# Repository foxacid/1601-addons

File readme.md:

# 1601 Clone Add-Ons

This repository contains a front panel design and divider add-on (circuit design by [Matthias Herrmann aka Fonik](http://www.modular.fonik.de/)) for the [1601 clone project by Kipling](https://www.muffwiggler.com/forum/viewtopic.php?t=110640).

## One Thousand Six Hundred and One Panel 

Just like the [TTSH](http://www.thehumancomparator.net/) panel, this 1601 front panel design is inspired by the ARP 2600 'Grey Meanie' layout and colour scheme. To match the TTSH, the text is set in 9pt Helvetica (white on RAL 7016 Anthrazitgrau).

The layout fits Kiplings 1601 clone PCBS Rev 1-3. Additionally there is a provision for 6 extra jacks above the power switch to the right to accomodate the Clock Divider add-on.

## Divider PCB

The Clock Divider is based on an [original design by Matthias Herrmann](http://www.modular.fonik.de/pdf/SimpleDividerSCH.pdf) - thanks Matthias! The clock-divider folder contains the EAGLE source files and Gerbers generated with [Seeed Studio](https://www.seeedstudio.com/) design rules. A unipolar +15V power source is required.

There is a provision for normalising Gate Output 2 to the divider's clock input. There are also provisions for LED indicators and a manual Reset button. Those are not present on the front panel.

### PCB

### Bill of Materials

 - - - -
**Make sure to use 15V versions for the logic ICs**
 - - - -

Name                 |  Value       |  Package 
-----------------    | ------------ | ------------
***Capacitors***     |              |         
C1                   |  100uF       |  Radial, 2.5mm spacing
C2                   |  0.1µF       |  0805
C3                   |  0.1µF       |  0805
C5                   |  0.01µF      |  0805
***Semiconductors*** |              |         
D1-D4                |  1N4148      |  DO35 
Q1-Q7                |  BC850       |  SOT23
IC1                  |  4024D       |  SO14
IC2                  |  4069D       |  SO14
***Resistors***      |              |      
R1                   |  47K         |  0805
R2                   |  10K         |  0805
R3                   |  47K         |  0805
R4                   |  100K        |  0805
R5                   |  100K        |  0805
R6                   |  10K         |  0805
R7                   |  10K         |  0805
R8                   |  47K         |  0805
R10                  |  2K2         |  0805
R11                  |  1K          |  0805
R12                  |  2K2         |  0805
R13                  |  2K2         |  0805
R14                  |  1K          |  0805
R15                  |  2K2         |  0805
R16                  |  2K2         |  0805
R17                  |  1K          |  0805
R18                  |  2K2         |  0805
R19                  |  2K2         |  0805
R20                  |  1K          |  0805
R21                  |  2K2         |  0805
***Jacks***          |              |    
CLOCK                |  PJ301BM     |  3,5mm Mono
RESET                |  PJ301BM     |  3,5mm Mono
F/2                  |  PJ301BM     |  3,5mm Mono
F/4                  |  PJ301BM     |  3,5mm Mono
F/8                  |  PJ301BM     |  3,5mm Mono
F/16                 |  PJ301BM     |  3,5mm Mono

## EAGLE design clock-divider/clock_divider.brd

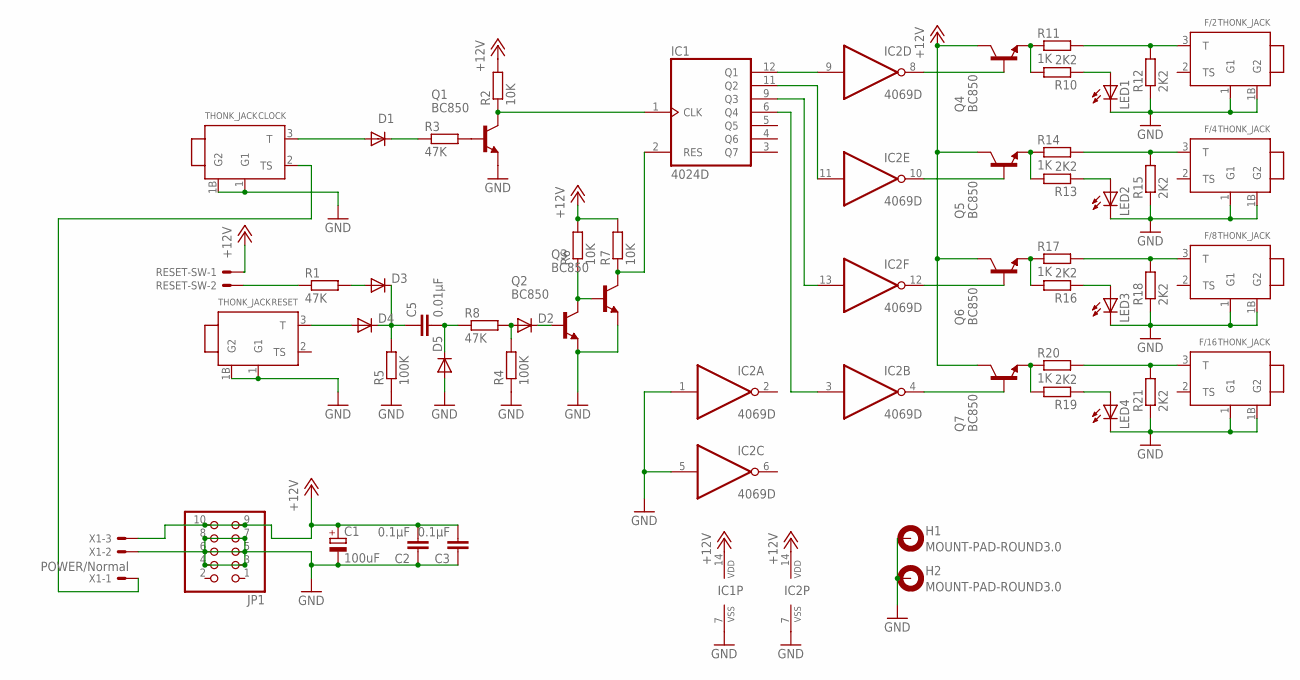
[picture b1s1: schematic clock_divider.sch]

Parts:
C1: 100uF; E2,5-6E
C2, C3: 0.1µF; C0805
C5: 0.01µF; C0805
CLOCK: THONK_JACK; THONK_JACK_P
D1, D2, D3, D4, D5: 1N4148; DO35-7
F/2, F/4, F/8, F/16: THONK_JACK; THONK_JACK_P
H1, H2: MOUNT-PAD-ROUND3.0; 3,0-PAD
IC1: 4024D; SO14
IC2: 4069D; SO14
JP1: PINHD-2X5; 2X05
LED1, LED2, LED3, LED4: LED5MM
Q1, Q2, Q3, Q4, Q5, Q6, Q7: BC850; SOT23
R1, R3, R8: 47K; M0805
R2, R6, R7: 10K; M0805
R4, R5: 100K; M0805
R10, R12, R13, R15, R16, R18, R19, R21: 2K2; M0805
R11, R14, R17, R20: 1K; M0805
RESET: THONK_JACK; THONK_JACK_P
RESET-SW: KK-156-2
X1: POWER/Normal; KK-156-3

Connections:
+12V: C1.+, C2.2, C3.2, IC1.14 (VDD), IC2.14 (VDD), JP1.9, JP1.10, Q4.3 (C), Q5.3 (C), Q6.3 (C), Q7.3 (C), R2.2, R6.2, R7.2, RESET-SW.1, X1.3
GND: C1.-, C2.1, C3.1, CLOCK.1 (G1), CLOCK.1B (G2), D5.A, F/2.1 (G1), F/2.1B (G2), F/4.1 (G1), F/4.1B (G2), F/8.1 (G1), F/8.1B (G2), F/16.1 (G1), F/16.1B (G2), H1.B3,0, H2.B3,0, IC1.7 (VSS), IC2.1 (I), IC2.5 (I), IC2.7 (VSS), JP1.3, JP1.4, JP1.5, JP1.6, JP1.7, JP1.8, LED1.K (C), LED2.K (C), LED3.K (C), LED4.K (C), Q1.2 (E), Q2.2 (E), Q3.2 (E), R4.1, R5.1, R12.1, R15.1, R18.1, R21.1, RESET.1 (G1), RESET.1B (G2), X1.2
unnamed: Q4.2 (E), R10.2, R11.1
unnamed: IC1.12 (Q1), IC2.9 (I)
unnamed: IC1.11 (Q2), IC2.11 (I)
unnamed: Q1.1 (B), R3.2
unnamed: IC1.1 (CLK), Q1.3 (C), R2.1
unnamed: D1.C, R3.1
unnamed: CLOCK.3 (T), D1.A
unnamed: D4.A, RESET.3 (T)
unnamed: C5.1, D3.C, D4.C, R5.2
unnamed: C5.2, D5.C, R8.1
unnamed: D2.A, R4.2, R8.2
unnamed: D2.C, Q2.1 (B)
unnamed: Q2.3 (C), Q3.1 (B), R6.1
unnamed: IC1.2 (RES), Q3.3 (C), R7.1
unnamed: IC1.9 (Q3), IC2.13 (I)
unnamed: IC1.6 (Q4), IC2.3 (I)
unnamed: LED2.A, R13.1
unnamed: IC2.8 (O), Q4.1 (B)
unnamed: LED4.A, R19.1
unnamed: F/4.3 (T), R14.2, R15.2
unnamed: Q5.2 (E), R13.2, R14.1
unnamed: IC2.10 (O), Q5.1 (B)
unnamed: F/8.3 (T), R17.2, R18.2
unnamed: Q6.2 (E), R16.2, R17.1
unnamed: IC2.12 (O), Q6.1 (B)
unnamed: F/16.3 (T), R20.2, R21.2
unnamed: Q7.2 (E), R19.2, R20.1
unnamed: IC2.4 (O), Q7.1 (B)
unnamed: LED3.A, R16.1
unnamed: LED1.A, R10.1
unnamed: D3.A, R1.2
unnamed: R1.1, RESET-SW.2
unnamed: CLOCK.2 (TS), X1.1
unnamed: F/2.3 (T), R11.2, R12.2

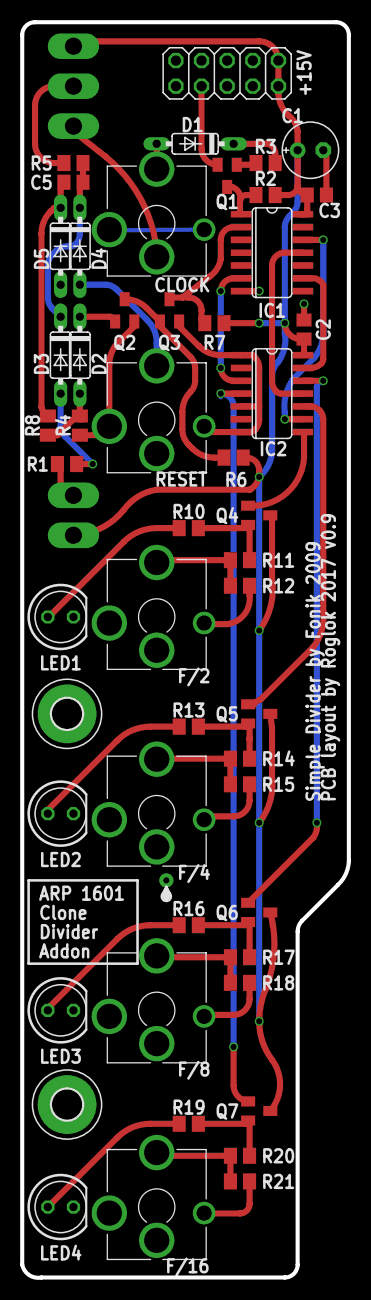
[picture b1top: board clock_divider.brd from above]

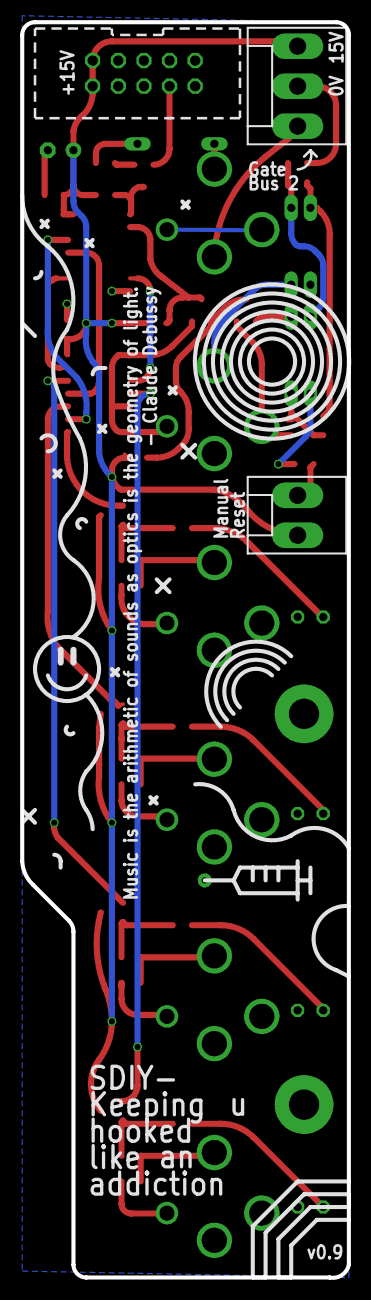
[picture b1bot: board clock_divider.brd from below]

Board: 2 copper layers, 32.4 x 124.5 mm, 53 parts (2 on the bottom side), 36 nets.

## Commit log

2017-02-22 Update docs
2017-02-22 Fix image paths
2017-02-22 Fix panel URL
2017-02-23 Resize PCB images
2017-02-23 Add BOM
2017-02-23 Update panel render
2017-04-06 Add measurement and drilling patterns
2017-04-22 Update Thonk Jack description
2017-04-22 Update Jack description
2017-10-03 Add note to use high voltage version for 4024
